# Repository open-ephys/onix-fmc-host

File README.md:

# ONIX FMC Host
This card provides a host interface for serialized headstages and miniscopes, as
well as general purpose analog and digital IO. It is a VITA-57.1
compliant module that uses high pin-count FMC connector. In combination with a
base FPGA board (e.g. [Numato Lab
Nereid](https://numato.com/product/nereid-kintex-7-pci-express-fpga-development-board),
it provides host PC communication for the following:

- Two deserailizers for any multifunction headstage conforming to the ONIX
  serialization protocol
- 12x 16-bit, +/-10V analog outputs or inputs. Direction selected via analog
  switch controllable over the FMC connector. Analog inputs are separated into
  2 simultaneously sampled 6-channel banks. 
- Analog output are always looped back using the analog inputs.
- 3x high speed LVDS input pairs
- 2x high speed LVDS outputs pairs
- 2x high speed, arbitrary logic-level, singled-ended Hi-Z or 50-ohm clock inputs
- 1x high speed single ended, 50-ohm clock output
- 4x MLVDS input or output trigger lines

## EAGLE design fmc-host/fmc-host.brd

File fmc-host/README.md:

# FMC Host PCB
Circuit design and manufacturing files for the ONIX FMC Host board.

## Bill of Materials
The bill of materials for this device can be found
[here](https://docs.google.com/spreadsheets/d/1dfK3jICU-dsLt_pm781gltwNn1_-4-RHdhAkIiad6z8/edit?usp=sharing).

## Manufacturing Requirements
In order to meet approximately correct trace impedances, the design assumes the
following stackup:

1. Top Copper 0.035 mm
1. Prepreg (2313) 0.1 mm
1. Inner Copper 0.0175 mm
1. Core (Copper) 0.565 mm
1. Inner Copper 0.0175 mm
1. Prepreg (2116) 0.127 mm
1. Inner Copper 0.0175 mm
1. Core (Copper) 0.565 mm
1. Inner Copper 0.0175 mm
1. Prepreg (2313) 0.1 mm
1. Bottom Copper 0.0175 mm

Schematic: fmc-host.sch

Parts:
C1, C2, C5, C6, C26, C27, C34, C35, C36, C37, C70, C71, C72, C73, C79, C80, C81, C91, C92, C106, C118, C139, C140: 10uF; 1206
C3, C4, C7, C8, C9, C10, C13, C14, C15, C16, C17, C18, C19, C22, C23, C30, C31, C32, C33, C41, C43, C44, C45, C46, C47, C48, C49, C52, C53, C54, C55, C56, C60, C61, C63, C65, C67, C68, C78, C83, C84, C85, C86, C87, C89, C90, C93, C99, C100, C104, C107, C110, C111, C112, C114, C115, C132, C134, C135, C137, C138: 0.1uF; 0402
C11, C12, C20, C21, C24, C25, C50, C51, C57, C58, C82, C122, C123, C124: 10nF; 0402
C28, C29: 4.7nF; 0402
C38, C39: 47nF; 0402
C40, C42, C64, C66, C74, C75, C76, C88: 1uF; 0805
C59, C62, C69, C77, C95, C96, C101, C103, C105, C108, C109, C113, C116, C117, C119, C120, C121, C125, C126, C127: 10uF; 0805
C94, C97, C98, C102, C130, C131: 47uF; 1210
C128, C129: 0.1uF, 500V; 1210
C133, C136: 33uF; 1411-VISHAY-B
D1, D2: SESD0402X1UN-0020-090; 0402P-DFN
D3, D4, D5: BAR66; SOT23
D6: KDZ4.3B; SOD123
F1, F2, F3: C014F-2; 1812
J1, J2, J3, J4, J5: SMA002; MMCX-THRU
J6: FTSH-105-01-F-D-RA-K
J7: 12226-8250-00FR; 12226-82X0-00XX
J8: FMC_SINGLE_WIDTH_MODULE
J9: ASP-134488-01; FMC_HPC_MALE
J10: BM08B-SURS-TF
L1, L2: 1008PS-472; 1008PS
L3, L4, L9, L10, L11, L12: BLM18KG601SN1D; 0603
L5, L6: SRNxx-101M; SRN6045TA
L7, L8: MPZ2012S102AT000; 0805
L13: 1277AS-H-6R8M=P2; 1210
L14, L15, L16, L17, L18, L19: BLM15PX601SN1D; 0402; PARTNO BLM15PX601SN1D
Q1, Q2: SI1012R; SC75
R1, R2, R38, R39: 3k; 0402
R3, R4, R9, R10, R57, R58: 2k; 0402
R5, R6, R7, R8, R11, R12: 150,0.25W; 0603
R13, R14, R49, R50, R51, R52, R76: 165k; 0402
R15, R16, R35, R37, R59, R64, R65, R66, R67, R68, R78, R79: 10k; 0402
R17, R18, R41, R42, R44, R45, R46, R47: 1k; 0402
R19, R21: 5.6k 1%; 0402
R20, R22: 21k 1%; 0402
R23, R24, R28, R29: 49.9; 0402
R25, R26, R27: 100; 0402
R30, R31, R32, R33, R40, R43, R71, R73, R75: 4.7k; 0402
R34, R36: DNP; 0402
R48, R63: 0; 0402
R53, R54, R55, R56: 2.2k; RN2X8-1506
R60, R61: 3.48k; 0402
R62: 649k; 0402
R69: 2.2k; 0402
R70: 15k; 0402
R72, R74: 47k; 0402
R77: 178k; 0402
R80, R81: 73.2k; 0402
S1, S2: CHS-01TA; DIP01-SMD-GULL
S3: CHS-02TB
TP1, TP2, TP4, TP5, TP6, TP7, TP11, TP12, TP13, TP14, TP15, TP16: TPB1,27; B1,27
TP3, TP8, TP9, TP10, TP17, TP18: TPB2,54; B2,54
U1: SN74LVC2G34DCKR; SC70
U2: SN65LVDS9638DGN; MSOP-8-PAD-3X3
U3: FIN1032MTCX; TSSOP-16
U4, U5: ADCMP600; SOT-23-5
U6, U7, U8: DG1412E; QFN16-4X4MM
U9, U10: DS90UB934-Q1; WQFN48-7X7-PAD
U11: DS91M040; WQFN32-5X5
U12: AD5766BCPZ-RL7; CP_40_7
U13: MCP47FEB02A0-E/ST; TSSOP-8
U14: LM4132AMF-2.5/NOPBCT-ND; SOT-23-5
U15: AD7617BSTZ; ST_80_2
U16: AD5142BCPZ10; TSSOP-16_4.4X5.0
U17: LTM4622A; BGA_5X5_625X625
U19, U20: TPS7A49; PVSON-N8+4-3X3
U21: TPS7A30; PVSON-N8+4-3X3
U22: 24AA64ST; TSSOP8
U23: LTM8049_BGA; LTM8049
U24: TPS62061DSGT; WSON8-2X2
X2: OE-LOGO_7X5; OE-LOGO-7X5

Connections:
!ADC_CS: J9.H13 (LA07_P), U15.63 (!CS)
!ADC_RESET: J9.F10 (HA08_P), R66.2
!DAC_CS: J9.J16 (HA14_N), U12.8 (!CS)
!DAC_RESET: J9.F14 (HA12_N), U12.3 (!RESET)
!LINK_PWR_ADJ_CS: J9.F38 (HB20_N), U16.16 (!CS)
!LINK_PWR_ADJ_RESET: J9.E37 (HB21_N), U16.2 (!RESET)
$N1: D5.3 (COMM), F2.2, R2.2, R6.2, R8.2, R12.2, R24.1
$N2: D3.3 (COMM), F3.2, U1.4 (OUT2), U1.6 (OUT1)
$N3: D4.3 (COMM), F1.2, R1.2, R5.2, R7.2, R11.2, R23.1
+1V8: C86.2, C87.2, C91.2, C92.2, C106.2, L3.2, L4.2, L9.1, L10.1, L13.1, R19.1, R21.1, R34.1, R36.1, TP16.TP, U9.17 (VDD18), U10.17 (VDD18), U24.4 (FB)
+3V3: C10.2, C22.1, C23.1, C28.1, C29.1, C32.1, C33.1, C74.2, C78.2, C82.2, C89.2, C93.2, C96.2, C111.2, C113.2, C114.2, C117.2, C118.2, C136.A (+), C137.2, C138.2, C139.1, C140.1, J9.E39 (VADJ), J9.F40 (VADJ), J9.G39 (VADJ), J9.H40 (VADJ), J9.J39 (VIO_B_M2C), J9.K40 (VIO_B_M2C), L11.1, L12.1, R30.2, R31.2, R32.2, R33.2, R40.2, R43.2, R57.2, R58.2, R63.1, R64.1, R65.1, R69.1, R78.2, R79.2, S1.2, S2.2, TP11.TP, U1.5 (VCC), U2.1 (VCC), U3.4 (EN), U3.16 (VCC), U4.5 (V+), U5.5 (V+), U9.4 (OSS_SEL), U9.5 (OEN), U10.4 (OSS_SEL), U10.5 (OEN), U11.11 (VDD), U11.12 (VDD), U11.29 (VDD), U11.30 (VDD), U12.4 (VLOGIC), U13.1 (VDD), U13.2 (REFA), U15.49 (VDRIVE), U16.1 (INDEP), U16.11 (VDD), U16.12 (VLOGIC), U23.A5 (VIN1), U23.A6 (VIN1), U23.A7 (VIN1), U23.B7 (RUN1), U23.K7 (RUN2), U23.L5 (VIN2), U23.L6 (VIN2), U23.L7 (VIN2), U24.5 (EN), U24.6 (MODE), U24.7 (AVIN), U24.8 (PVIN)
+5V_AN: C59.2, C62.2, C69.2, C77.2, C81.1, C83.2, C84.2, C85.2, C90.2, C107.2, C108.2, L14.1, TP1.TP, U12.28 (AVCC), U14.3 (EN), U14.4 (VIN), U15.6 (VCC), U15.15 (VCC), U15.30 (VCC), U15.71 (VCC)
+12V: C116.2, C133.A (+), C134.2, C135.2, J7.1, J7.26, J9.C35 (12P0V1), J9.C37 (12P0V2), R38.2, R39.2, TP12.TP, U17.A2 (VIN), U17.B3 (VIN), U17.D3 (VIN), U17.E2 (VIN)
+13V_AN: C7.2, C8.2, C9.2, C104.2, C105.2, L15.1, TP2.TP, U6.11 (V+), U7.11 (V+), U8.11 (V+), U12.26 (AVDD)
+15V: C130.2, L17.2, L18.2, R76.1, U23.A1 (VOUT1P), U23.A2 (VOUT1P), U23.B1 (VOUT1P), U23.B2 (VOUT1P)
-13V_AN: C17.2, C18.2, C19.2, C99.2, C103.2, L16.1, TP4.TP, U6.2 (V-), U6.PAD (V-), U7.2 (V-), U7.PAD (V-), U8.2 (V-), U8.PAD (V-), U12.6 (AVSS), U12.PAD (AVSS)
-15V: C131.1, L19.2, R77.1, U23.G1 (VOUT2N), U23.G2 (VOUT2N), U23.H1 (VOUT2N), U23.H2 (VOUT2N), U23.J2 (VOUT2N)
ADC_BUSY: J9.J12 (HA11_P), U15.67 (BUSY)
ADC_CONVST: J9.K13 (HA10_P), U15.68 (CONVST)
ADC_MISO_A: J9.K11 (HA06_N), U15.57 (DB12/SDOA)
ADC_MISO_B: J9.J10 (HA07_N), U15.56 (DB11/SDOB)
ADC_MOSI: J9.K10 (HA06_P), U15.55 (DB10/SDI)
ADC_SCLK: J9.J13 (HA11_N), U15.62 (SCLK/!RD)
ADDR0: J9.C27 (LA27_N), R78.1, S3.4
ADDR1: J9.C26 (LA27_P), R79.1, S3.3
AGND: C7.1, C8.1, C9.1, C17.1, C18.1, C19.1, C59.1, C62.1, C69.1, C77.1, C81.2, C83.1, C84.1, C85.1, C88.1, C90.1, C95.1, C99.1, C100.1, C101.1, C103.1, C104.1, C105.1, C107.1, C108.1, J7.13, J7.14, R48.1, R53.C2, R53.C4, R53.C6, R53.C7, R54.C1, R54.C3, R54.C5, R54.C6, R54.C7, R54.C8, R55.C2, R55.C3, R55.C5, R55.C7, R56.C1, R56.C2, R56.C3, R56.C4, R56.C6, R56.C8, TP3.TP, U6.3 (GND), U7.3 (GND), U8.3 (GND), U12.10 (AGND), U12.20 (NIC), U12.23 (N0), U12.24 (N1), U12.25 (NIC), U12.29 (AGND), U12.31 (NIC), U14.2 (GND), U15.5 (AGND), U15.16 (AGND), U15.29 (AGND), U15.32 (REFGND), U15.34 (REFINOUTGND), U15.69 (REGGND), U15.72 (AGND)
AIN_AOUT0: J9.F11 (HA08_N), U8.15 (IN1)
AIN_AOUT1: J9.D11 (LA05_P), U8.6 (IN4)
AIN_AOUT2: J9.E12 (HA13_P), U8.7 (IN3)
AIN_AOUT3: J9.H10 (LA04_P), U8.14 (IN2)
AIN_AOUT4: J9.E18 (HA20_P), U7.15 (IN1)
AIN_AOUT5: J9.J9 (HA07_P), U7.6 (IN4)
AIN_AOUT6: J9.G10 (LA03_N), U7.7 (IN3)
AIN_AOUT7: J9.F17 (HA15_N), U7.14 (IN2)
AIN_AOUT8: J9.H20 (LA15_N), U6.7 (IN3)
AIN_AOUT9: J9.J19 (HA18_N), U6.14 (IN2)
AIN_AOUT10: J9.G19 (LA16_N), U6.6 (IN4)
AIN_AOUT11: J9.H19 (LA15_P), U6.15 (IN1)
AIO_0: J7.7, R53.C1, U8.16 (D1)
AIO_1: J7.20, R53.C3, U8.5 (D4)
AIO_2: J7.8, R53.C5, U8.8 (D3)
AIO_3: J7.21, R53.C8, U8.13 (D2)
AIO_4: J7.9, R54.C4, U7.16 (D1)
AIO_5: J7.22, R54.C2, U7.5 (D4)
AIO_6: J7.10, R56.C5, U7.8 (D3)
AIO_7: J7.23, R56.C7, U7.13 (D2)
AIO_8: J7.11, R55.C6, U6.8 (D3)
AIO_9: J7.24, R55.C8, U6.13 (D2)
AIO_10: J7.12, R55.C4, U6.5 (D4)
AIO_11: J7.25, R55.C1, U6.16 (D1)
AOUT0: U6.1 (S1), U12.32 (VOUT0)
AOUT1: U6.4 (S4), U12.33 (VOUT1)
AOUT2: U6.9 (S3), U12.34 (VOUT2)
AOUT3: U6.12 (S2), U12.35 (VOUT3)
AOUT4: U7.1 (S1), U12.36 (VOUT4)
AOUT5: U7.4 (S4), U12.37 (VOUT5)
AOUT6: U7.12 (S2), U12.38 (VOUT6)
AOUT7: U7.9 (S3), U12.39 (VOUT7)
AOUT8: U8.9 (S3), U12.12 (VOUT8)
AOUT9: U8.12 (S2), U12.13 (VOUT9)
AOUT10: U8.4 (S4), U12.14 (VOUT10)
AOUT11: U8.1 (S1), U12.15 (VOUT11)
CLKIN0: J9.D21 (LA17_N_CC), TP7.TP, U4.1 (OUT)
CLKIN1: J9.E19 (HA20_N), TP6.TP, U5.1 (OUT)
CLKIN_TERM0: J9.K19 (HA21_P), R17.1
CLKIN_TERM1: J9.K17 (HA17_N_CC), R18.1
CLKIN_VBIAS_SCL: J9.J21 (HA22_P), R58.1, U13.7 (SCL)
CLKIN_VBIAS_SDA: J9.K20 (HA21_N), R57.1, U13.8 (SDA)
CLKOUT: J9.D20 (LA17_P_CC), U1.1 (IN3), U1.3 (IN2)
DAC_MISO: J9.K16 (HA17_P_CC), U12.9 (MISO)
DAC_MOSI: J9.H14 (LA07_N), U12.5 (MOSI)
DAC_MUX: TP15.TP, U12.27 (MUX_OUT)
DAC_SCLK: J9.J15 (HA14_P), U12.7 (SCLK)
DES_A_D0: J9.F34 (HB16_P), U10.24 (ROUT0)
DES_A_D1: J9.K35 (HB14_N), U10.23 (ROUT1)
DES_A_D2: J9.J34 (HB15_N), U10.22 (ROUT2)
DES_A_D3: J9.K34 (HB14_P), U10.21 (ROUT3)
DES_A_D4: J9.E33 (HB19_P), U10.19 (ROUT4)
DES_A_D5: J9.J33 (HB15_P), U10.18 (ROUT5)
DES_A_D6: J9.F32 (HB12_N), U10.16 (ROUT6)
DES_A_D7: J9.E31 (HB13_N), U10.15 (ROUT7)
DES_A_D8: J9.K32 (HB10_N), U10.14 (ROUT8)
DES_A_D9: J9.F31 (HB12_P), U10.13 (ROUT9)
DES_A_D10: J9.J31 (HB11_N), U10.12 (ROUT10)
DES_A_D11: J9.K31 (HB10_P), U10.11 (ROUT11)
DES_A_GPIO0: J9.J37 (HB18_N), U10.28 (GPIO0)
DES_A_GPIO1: J9.K37 (HB17_P_CC), U10.27 (GPIO1)
DES_A_GPIO2: J9.J36 (HB18_P), U10.26 (GPIO2)
DES_A_GPIO3: J9.E34 (HB19_N), R43.1, U10.25 (GPIO3/INTB)
DES_A_HSYNC: J9.E30 (HB13_P), U10.10 (HSYNC)
DES_A_LOCK: J9.E27 (HB09_P), R50.2, U10.48 (LOCK)
DES_A_PASS: J9.J28 (HB07_N), R52.2, U10.47 (PASS)
DES_A_PCLK: J9.K28 (HB06_P_CC), U10.8 (PCLK)
DES_A_PDB: J9.F35 (HB16_N), U10.30 (PDB)
DES_A_SCL: J9.F29 (HB08_N), R31.1, U10.2 (SCL)
DES_A_SDA\: J9.E28 (HB09_N), R33.1, U10.1 (SDA)
DES_A_VSYNC: J9.J30 (HB11_P), U10.9 (VSYNC)
DES_B_D0: J9.H29 (LA24_N), U9.24 (ROUT0)
DES_B_D1: J9.H28 (LA24_P), U9.23 (ROUT1)
DES_B_D2: J9.G28 (LA25_N), U9.22 (ROUT2)
DES_B_D3: J9.G27 (LA25_P), U9.21 (ROUT3)
DES_B_D4: J9.D27 (LA26_N), U9.19 (ROUT4)
DES_B_D5: J9.D26 (LA26_P), U9.18 (ROUT5)
DES_B_D6: J9.H26 (LA21_N), U9.16 (ROUT6)
DES_B_D7: J9.G25 (LA22_N), U9.15 (ROUT7)
DES_B_D8: J9.H25 (LA21_P), U9.14 (ROUT8)
DES_B_D9: J9.D24 (LA23_N), U9.13 (ROUT9)
DES_B_D10: J9.G24 (LA22_P), U9.12 (ROUT10)
DES_B_D11: J9.D23 (LA23_P), U9.11 (ROUT11)
DES_B_GPIO0: J9.H32 (LA28_N), U9.28 (GPIO0)
DES_B_GPIO1: J9.G31 (LA29_N), U9.27 (GPIO1)
DES_B_GPIO2: J9.H31 (LA28_P), U9.26 (GPIO2)
DES_B_GPIO3: J9.G30 (LA29_P), R40.1, U9.25 (GPIO3/INTB)
DES_B_HSYNC\: J9.H23 (LA19_N), U9.10 (HSYNC)
DES_B_LOCK: J9.J22 (HA22_N), R49.2, U9.48 (LOCK)
DES_B_PASS: J9.K22 (HA23_P), R51.2, U9.47 (PASS)
DES_B_PCLK: J9.C22 (LA18_P_CC), U9.8 (PCLK)
DES_B_PDB: J9.G33 (LA31_P), U9.30 (PDB)
DES_B_SCL: J9.G22 (LA20_N), R30.1, U9.2 (SCL)
DES_B_SDA: J9.H22 (LA19_P), R32.1, U9.1 (SDA)
DES_B_VSYNC: J9.K23 (HA23_N), U9.9 (VSYNC)
DI_VBIAS0: R15.1, U13.3 (VOUT0)
DI_VBIAS1: R16.1, U13.4 (VOUT1)
DOUTP_F_A: C45.2, D2.C, J2.SIG (1), L2.2, R4.2
DOUTP_F_B: C44.2, D1.C, J1.SIG (1), L1.2, R3.2
FMC_PG: J9.D1 (PG_C2M), J9.F1 (PG_M2C)
GND: C1.1, C2.1, C3.1, C4.1, C5.1, C6.1, C10.1, C11.1, C12.1, C13.2, C14.2, C15.2, C16.2, C20.1, C21.1, C22.2, C23.2, C24.1, C25.1, C26.1, C27.1, C28.2, C29.2, C30.2, C31.2, C32.2, C33.2, C34.1, C35.1, C36.1, C37.1, C40.1, C41.1, C42.1, C43.1, C46.1, C47.1, C48.1, C49.1, C50.1, C51.1, C52.1, C53.1, C54.1, C55.1, C56.1, C57.1, C58.1, C60.1, C61.1, C63.1, C64.1, C65.1, C66.1, C67.1, C68.1, C70.1, C71.1, C72.1, C73.1, C74.1, C75.1, C76.1, C78.1, C79.1, C80.1, C82.1, C86.1, C87.1, C89.1, C91.1, C92.1, C93.1, C94.1, C96.1, C97.1, C98.1, C102.1, C106.1, C109.1, C110.1, C111.1, C112.1, C113.1, C114.1, C115.2, C116.1, C117.1, C118.1, C119.1, C120.1, C121.1, C122.2, C123.2, C124.2, C125.1, C126.1, C127.1, C128.1, C129.1, C130.1, C131.2, C132.1, C133.C (-), C134.1, C135.1, C136.C (-), C137.1, C138.1, C139.2, C140.2, D1.A, D2.A, D3.1 (A), D4.1 (A), D5.1 (A), D6.A, J1.GND@1 (2), J1.GND@2 (2), J1.GND@3 (2), J1.GND@4 (2), J2.GND@1 (2), J2.GND@2 (2), J2.GND@3 (2), J2.GND@4 (2), J3.GND@1 (2), J3.GND@2 (2), J3.GND@3 (2), J3.GND@4 (2), J4.GND@1 (2), J4.GND@2 (2), J4.GND@3 (2), J4.GND@4 (2), J5.GND@1 (2), J5.GND@2 (2), J5.GND@3 (2), J5.GND@4 (2), J7.PAD1, J7.PAD2, J9.A1 (GND), J9.A4 (GND), J9.A5 (GND), J9.A8 (GND), J9.A9 (GND), J9.A12 (GND), J9.A13 (GND), J9.A16 (GND), J9.A17 (GND), J9.A20 (GND), J9.A21 (GND), J9.A24 (GND), J9.A25 (GND), J9.A28 (GND), J9.A29 (GND), J9.A32 (GND), J9.A33 (GND), J9.A36 (GND), J9.A37 (GND), J9.A40 (GND), J9.B2 (GND), J9.B3 (GND), J9.B6 (GND), J9.B7 (GND), J9.B10 (GND), J9.B11 (GND), J9.B14 (GND), J9.B15 (GND), J9.B18 (GND), J9.B19 (GND), J9.B22 (GND), J9.B23 (GND), J9.B26 (GND), J9.B27 (GND), J9.B30 (GND), J9.B31 (GND), J9.B34 (GND), J9.B35 (GND), J9.B38 (GND), J9.B39 (GND), J9.C1 (GND), J9.C4 (GND), J9.C5 (GND), J9.C8 (GND), J9.C9 (GND), J9.C12 (GND), J9.C13 (GND), J9.C16 (GND), J9.C17 (GND), J9.C20 (GND), J9.C21 (GND), J9.C24 (GND), J9.C25 (GND), J9.C28 (GND), J9.C29 (GND), J9.C32 (GND), J9.C33 (GND), J9.C34 (GA0), J9.C36 (GND), J9.C38 (GND), J9.C40 (GND), J9.D2 (GND), J9.D3 (GND), J9.D6 (GND), J9.D7 (GND), J9.D10 (GND), J9.D13 (GND), J9.D16 (GND), J9.D19 (GND), J9.D22 (GND), J9.D25 (GND), J9.D28 (GND), J9.D35 (GA1), J9.D37 (GND), J9.D39 (GND), J9.E1 (GND), J9.E4 (GND), J9.E5 (GND), J9.E8 (GND), J9.E11 (GND), J9.E14 (GND), J9.E17 (GND), J9.E20 (GND), J9.E23 (GND), J9.E26 (GND), J9.E29 (GND), J9.E32 (GND), J9.E35 (GND), J9.E38 (GND), J9.E40 (GND), J9.F2 (GND), J9.F3 (GND), J9.F6 (GND), J9.F9 (GND), J9.F12 (GND), J9.F15 (GND), J9.F18 (GND), J9.F21 (GND), J9.F24 (GND), J9.F27 (GND), J9.F30 (GND), J9.F33 (GND), J9.F36 (GND), J9.F39 (GND), J9.G1 (GND), J9.G4 (GND), J9.G5 (GND), J9.G8 (GND), J9.G11 (GND), J9.G14 (GND), J9.G17 (GND), J9.G20 (GND), J9.G23 (GND), J9.G26 (GND), J9.G29 (GND), J9.G32 (GND), J9.G35 (GND), J9.G38 (GND), J9.G40 (GND), J9.H2 (PRSNT_M2C_L), J9.H3 (GND), J9.H6 (GND), J9.H9 (GND), J9.H12 (GND), J9.H15 (GND), J9.H18 (GND), J9.H21 (GND), J9.H24 (GND), J9.H27 (GND), J9.H30 (GND), J9.H33 (GND), J9.H36 (GND), J9.H39 (GND), J9.J1 (GND), J9.J4 (GND), J9.J5 (GND), J9.J8 (GND), J9.J11 (GND), J9.J14 (GND), J9.J17 (GND), J9.J20 (GND), J9.J23 (GND), J9.J26 (GND), J9.J29 (GND), J9.J32 (GND), J9.J35 (GND), J9.J38 (GND), J9.J40 (GND), J9.K2 (GND), J9.K3 (GND), J9.K6 (GND), J9.K9 (GND), J9.K12 (GND), J9.K15 (GND), J9.K18 (GND), J9.K21 (GND), J9.K24 (GND), J9.K27 (GND), J9.K30 (GND), J9.K33 (GND), J9.K36 (GND), J9.K39 (GND), J10.2, J10.6, Q1.2 (S), Q2.2 (S), R1.1, R2.1, R13.1, R14.1, R20.2, R22.2, R28.2, R29.2, R35.2, R37.2, R48.2, R49.1, R50.1, R51.1, R52.1, R62.2, R67.2, R68.2, R71.1, R73.1, R75.1, R80.2, R81.2, S3.1, S3.2, TP8.TP, TP9.TP, TP10.TP, TP17.TP, TP18.TP, U1.2 (GND), U2.4 (GND), U2.PAD (GND), U3.8 (GND), U3.12 (!EN), U4.2 (V-), U5.2 (V-), U9.43 (RES1), U9.44 (RES2), U9.46 (SEL), U9.PAD (GND), U10.43 (RES1), U10.44 (RES2), U10.46 (SEL), U10.PAD (GND), U11.31 (GND), U11.PAD (GND), U12.2 (DGND), U13.5 (AVSS), U13.6 (LAT/HVC), U15.37 (SEQEN), U15.38 (HW_RNGSEL1), U15.39 (HW_RNGSEL0), U15.41 (DB0), U15.42 (DB1), U15.43 (DB2), U15.44 (DB3), U15.46 (DB5/CRCEN), U15.47 (DB6), U15.48 (DB7), U15.50 (DGND), U15.51 (REGGNDD), U15.53 (DB8), U15.54 (DB9), U15.58 (DB13/OS0), U15.59 (DB14/OS1), U15.60 (DB15/OS2), U15.61 (WR!/BURST), U15.64 (CHSEL0), U15.65 (CHSEL1), U15.66 (CHSEL2), U16.3 (GND), U16.5 (W1), U16.7 (VSS), U16.9 (W2), U17.B5 (GND), U17.C1 (GND), U17.C2 (GND), U17.C5 (SYNC/MODE), U17.D5 (GND), U19.3 (NC), U19.4 (GND), U19.PAD1 (PAD), U19.PAD2 (PAD), U19.PAD3 (PAD), U19.PAD4 (PAD), U19.PAD5 (PAD), U20.3 (NC), U20.4 (GND), U20.PAD1 (PAD), U20.PAD2 (PAD), U20.PAD3 (PAD), U20.PAD4 (PAD), U20.PAD5 (PAD), U21.3 (NC), U21.4 (GND), U21.PAD1 (PAD), U21.PAD2 (PAD), U21.PAD3 (PAD), U21.PAD4 (PAD), U21.PAD5 (PAD), U22.1 (A0), U22.2 (A1), U22.3 (A2), U22.4 (GND), U22.7 (WP), U23.A3 (GND), U23.A4 (GND), U23.B3 (GND), U23.B4 (GND), U23.B5 (GND), U23.B6 (GND), U23.C2 (VOUT1N), U23.C3 (GND), U23.C4 (GND), U23.C5 (GND), U23.C6 (GND), U23.D1 (VOUT1N), U23.D2 (VOUT1N), U23.D3 (GND), U23.D4 (GND), U23.D5 (GND), U23.D7 (SYNC1), U23.E1 (VOUT1N), U23.E2 (VOUT1N), U23.E3 (GND), U23.E4 (GND), U23.E5 (GND), U23.F1 (GND), U23.F2 (GND), U23.F5 (GND), U23.F6 (GND), U23.F7 (GND), U23.G3 (GND), U23.G4 (GND), U23.G5 (GND), U23.H3 (GND), U23.H4 (GND), U23.H5 (GND), U23.J3 (GND), U23.J4 (GND), U23.J5 (GND), U23.J6 (GND), U23.K1 (VOUT2P), U23.K2 (VOUT2P), U23.K3 (GND), U23.K4 (GND), U23.K5 (GND), U23.K6 (GND), U23.L1 (VOUT2P), U23.L2 (VOUT2P), U23.L3 (GND), U23.L4 (GND), U24.1 (PGND), U24.3 (AGND), U24.PAD (AGND)
LINK_A_PWR_EN: J9.H37 (LA32_P), R68.1, U17.B2 (RUN2)
LINK_B_PWR_EN: J9.K38 (HB17_N_CC), R67.1, U17.D2 (RUN1)
LINK_PWR_ADJ_MISO: J9.F37 (HB20_P), R69.2, U16.15 (MISO)
LINK_PWR_ADJ_MOSI: J9.E36 (HB21_P), U16.14 (MOSI)
LINK_PWR_ADJ_SCLK: J9.H38 (LA32_N), U16.13 (SCLK)
LVDS_DIN0: J9.J2 (CLK3_M2C_P), U3.3 (AOUT)
LVDS_DIN0_N: J7.4, R25.1, U3.1 (A-)
LVDS_DIN0_P: J7.17, R25.2, U3.2 (A+)
LVDS_DIN1: J9.H5 (CLK0_M2C_N), U3.5 (BOUT)
LVDS_DIN1_N: J7.16, R26.1, U3.7 (B-)
LVDS_DIN1_P: J7.3, R26.2, U3.6 (B+)
LVDS_DIN2: J9.H4 (CLK0_M2C_P), U3.11 (COUT)
LVDS_DIN2_N: J7.2, R27.1, U3.9 (C-)
LVDS_DIN2_P: J7.15, R27.2, U3.10 (C+)
LVDS_DOUT0: J9.J3 (CLK3_M2C_N), U2.2 (AIN)
LVDS_DOUT0_N: J7.19, U2.7 (AOUT-)
LVDS_DOUT0_P: J7.6, U2.8 (AOUT+)
LVDS_DOUT1: J9.K4 (CLK2_M2C_P), U2.3 (BIN)
LVDS_DOUT1_N: J7.18, U2.5 (BOUT-)
LVDS_DOUT1_P: J7.5, U2.6 (BOUT+)
MLVDS_CLK_0_N: J6.10, U11.24 (B0)
MLVDS_CLK_0_P: J6.09 (9), U11.23 (A0)
MLVDS_CLK_1_N: J6.08 (8), U11.22 (B1)
MLVDS_CLK_1_P: J6.07 (7), U11.21 (A1)
MLVDS_CLK_2_N: J6.04 (4), U11.20 (B2)
MLVDS_CLK_2_P: J6.03 (3), U11.19 (A2)
MLVDS_CLK_3_N: J6.02 (2), U11.18 (B3)
MLVDS_CLK_3_P: J6.01 (1), U11.17 (A3)
MLVDS_DE_!RE0: J9.F7 (HA04_P), U11.25 (DE0), U11.26 (!RE0)
MLVDS_DE_!RE1: J9.E7 (HA05_N), U11.27 (DE1), U11.28 (!RE1)
MLVDS_DE_!RE2: J9.H7 (LA02_P), U11.13 (!RE2), U11.14 (DE2)
MLVDS_DE_!RE3: J9.H8 (LA02_N), U11.15 (!RE3), U11.16 (DE3)
MLVDS_DI0: J9.F5 (HA00_N_CC), U11.2 (DI0)
MLVDS_DI1: J9.E2 (HA01_P_CC), U11.4 (DI1)
MLVDS_DI2: J9.E3 (HA01_N_CC), U11.6 (DI2)
MLVDS_DI3: J9.G3 (CLK1_M2C_N), U11.8 (DI3)
MLVDS_EN: J9.F8 (HA04_N), U11.10 (MDE)
MLVDS_RO0: J9.F4 (HA00_P_CC), U11.1 (RO0)
MLVDS_RO1: J9.G6 (LA00_P_CC), U11.3 (RO1)
MLVDS_RO2: J9.G7 (LA00_N_CC), U11.5 (RO2)
MLVDS_RO3: J9.G2 (CLK1_M2C_P), U11.7 (RO3)
unnamed: L13.2, U24.2 (SW)
unnamed: Q1.3 (D), R5.1, R7.1, R11.1
unnamed: R23.2, U4.3 (+IN)
unnamed: L1.1, L5.2, R3.1, R9.2
unnamed: R61.1, U17.A4 (FB2)
unnamed: F2.1, J4.SIG (1)
unnamed: Q2.3 (D), R6.1, R8.1, R12.1
unnamed: C110.2, U17.A3 (TRACK/SS2)
unnamed: R81.1, U23.G7 (RT2)
unnamed: R60.1, U17.E4 (FB1)
unnamed: F1.1, J3.SIG (1)
unnamed: C112.2, U17.E3 (TRACK/SS1)
unnamed: F3.1, J5.SIG (1)
unnamed: C125.2, L17.1, U19.5 (EN), U19.8 (IN)
unnamed: R80.1, U23.E7 (RT1)
unnamed: C13.1, R15.2, U4.4 (-IN)
unnamed: R24.2, U5.3 (+IN)
unnamed: C14.1, R16.2, U5.4 (-IN)
unnamed: L2.1, L6.2, R4.1, R10.2
unnamed: C6.2, C16.1, L6.1, L8.2, R10.1
unnamed: R55.1, U15.79 (V3B)
unnamed: C5.2, C15.1, L5.1, L7.2, R9.1
unnamed: R77.2, U23.J1 (FBX2)
unnamed: C45.1, U10.41 (RIN0+)
unnamed: C39.1, U10.42 (RIN0-)
unnamed: R76.2, U23.C1 (FBX1)
unnamed: C36.2, C42.2, C47.2, U10.3 (VDD11_D)
unnamed: C37.2, C43.2, U10.20 (VDD11_DVP)
unnamed: C39.2, R29.1
unnamed: C122.1, U19.6 (NR/SS)
unnamed: Q2.1 (G), R14.2, R18.2
unnamed: U23.E6 (CLKOUT1), U23.H7 (SYNC2)
unnamed: Q1.1 (G), R13.2, R17.2
unnamed: C44.1, U9.41 (RIN0+)
unnamed: R55.2, U15.80 (V3BGND)
unnamed: R70.1, R71.2, U19.2 (FB)
unnamed: C126.2, L18.1, U20.5 (EN), U20.8 (IN)
unnamed: C123.1, U20.6 (NR/SS)
unnamed: C68.2, C76.2, C80.2, U10.34 (VDD11_FPD)
unnamed: C115.1, R66.1, U15.36 (!RESET)
unnamed: C55.2, C60.2, C64.2, C71.2, L11.2, U9.7 (VDDIO), U9.29 (VDDIO)
unnamed: C34.2, C40.2, C46.2, U9.3 (VDD11_D)
unnamed: C35.2, C41.2, U9.20 (VDD11_DVP)
unnamed: C67.2, C75.2, C79.2, U9.34 (VDD11_FPD)
unnamed: C129.2, J9.CHASSIS_B (STANDOFF_B)
unnamed: C128.2, J9.CHASSIS_A (STANDOFF_A)
unnamed: J10.5, R42.2
unnamed: C38.1, U9.42 (RIN0-)
unnamed: R72.1, R73.2, U20.2 (FB)
unnamed: J10.7, R47.1
unnamed: C127.2, L19.1, U21.5 (EN), U21.8 (IN)
unnamed: C124.1, U21.6 (NR/SS)
unnamed: R74.1, R75.2, U21.2 (FB)
unnamed: R65.2, U15.45 (DB4/!SER1WR)
unnamed: R53.1, U15.28 (V0A)
unnamed: R64.2, U15.40 (SER/!PAR)
unnamed: C95.2, U15.31 (REFCAP)
unnamed: R53.2, U15.27 (V0AGND)
unnamed: J10.8, R41.1
unnamed: C109.2, U15.52 (REGCAPD)
unnamed: R55.8, U15.73 (V0B)
unnamed: C101.2, U15.70 (REGCAP)
unnamed: R63.2, U15.35 (REFSEL)
unnamed: R56.7, U15.2 (V4B)
unnamed: R56.1, U15.10 (V7BGND)
unnamed: R55.7, U15.74 (V0BGND)
unnamed: R55.6, U15.75 (V1B)
unnamed: R55.5, U15.76 (V1BGND)
unnamed: R55.4, U15.77 (V2B)
unnamed: R55.3, U15.78 (V2BGND)
unnamed: R53.3, U15.26 (V1A)
unnamed: R53.4, U15.25 (V1AGND)
unnamed: R53.5, U15.24 (V2A)
unnamed: R53.6, U15.23 (V2AGND)
unnamed: R53.8, U15.22 (V3A)
unnamed: R53.7, U15.21 (V3AGND)
unnamed: R54.2, U15.19 (V4A)
unnamed: R54.1, U15.20 (V4AGND)
unnamed: R54.4, U15.17 (V5A)
unnamed: R54.3, U15.18 (V5AGND)
unnamed: R54.5, U15.14 (V6A)
unnamed: R54.6, U15.13 (V6AGND)
unnamed: R54.7, U15.12 (V7A)
unnamed: R54.8, U15.11 (V7AGND)
unnamed: C38.2, R28.1
unnamed: R56.8, U15.1 (V4BGND)
unnamed: R56.5, U15.4 (V5B)
unnamed: R56.6, U15.3 (V5BGND)
unnamed: R56.4, U15.7 (V6B)
unnamed: R56.3, U15.8 (V6BGND)
unnamed: R56.2, U15.9 (V7B)
unnamed: R34.2, R35.1, U9.35 (IDX)
unnamed: J10.4, R45.1
unnamed: J10.3, R46.1
unnamed: J10.1, R44.1
unnamed: R60.2, U16.4 (A1)
unnamed: R61.2, U16.8 (A2)
unnamed: R62.1, U17.C4 (FREQ)
unnamed: C56.2, C61.2, C66.2, C73.2, L12.2, U10.7 (VDDIO), U10.29 (VDDIO)
unnamed: S2.1, U10.6 (BISTEN)
unnamed: R21.2, R22.1, U10.37 (MODE)
unnamed: R36.2, R37.1, U10.35 (IDX)
unnamed: C119.2, L14.2, R70.2, U19.1 (OUT)
unnamed: C120.2, L15.2, R72.2, U20.1 (OUT)
unnamed: C121.2, L16.2, R74.2, U21.1 (OUT)
unnamed: C100.2, R59.1, U15.33 (REFINOUT)
unnamed: S1.1, U9.6 (BISTEN)
unnamed: R19.2, R20.1, U9.37 (MODE)
PORT_A_BLUE: J9.G18 (LA16_P), R41.2
PORT_A_GREEN: J9.J18 (HA18_P), R47.2
PORT_A_RED: J9.H17 (LA11_N), R42.1
PORT_B_BLUE: J9.H16 (LA11_P), R45.2
PORT_B_GREEN: J9.G15 (LA12_P), R46.2
PORT_B_RED: J9.G13 (LA08_N), R44.2
SCL: J9.C30 (SCL), U22.6 (SCL)
SDA: J9.C31 (SDA), U22.5 (SDA)
TDI-TDO: J9.D30 (TDI), J9.D31 (TDO)
VAUX: C132.2, J9.D32 (3P3VAUX), U22.8 (VCC)
VDD_FPDX_A: C2.2, C4.2, C12.2, C21.2, C25.2, L4.1, U10.31 (VDD18_FPD1), U10.40 (VDD18_FPD0)
VDD_FPDX_B: C1.2, C3.2, C11.2, C20.2, C24.2, L3.1, U9.31 (VDD18_FPD1), U9.40 (VDD18_FPD0)
VDD_PX_A: C49.2, C51.2, C54.2, C58.2, C65.2, C72.2, L10.2, U10.36 (VDD18_P1), U10.45 (VDD18_P0)
VDD_PX_B: C48.2, C50.2, C53.2, C57.2, C63.2, C70.2, L9.2, U9.36 (VDD18_P1), U9.45 (VDD18_P0)
VLINK_A: C27.2, C31.1, C94.2, C97.2, L8.1, TP13.TP, U17.A1 (VOUT2), U17.B1 (VOUT2)
VLINK_B: C26.2, C30.1, C98.2, C102.2, L7.1, TP14.TP, U17.D1 (VOUT1), U17.E1 (VOUT1)
VREF: C88.2, R59.2, U12.22 (VREF), U14.5 (VOUT)
V_PROTECT: C52.2, D3.2 (C), D4.2 (C), D5.2 (C), D6.C, R38.1, R39.1, TP5.TP

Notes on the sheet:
FMC MEZZANINE
NB: Input protection voltage ~4.6V
L2 is the smallest package size I could find that barely meets current saturation requriements. An 8x8mm device that is probably safer is the Bourns SRN8040TA series.
Power: ~1.3A DC at 12V; 15.6W. With 90% efficiency regulation to 5.5V at serializer, this translates to 2.55A available, which is enough for 1A/LED + 500 mA serializer and FPGA.
DNP
NB: Use both MISO lines
NB: R-arrays provide input protection. Limit current thru internal clamp diodes to 10 mA at 20V.
NB: Worst case 100 mA draw from both ADC and DAC. With 10V stepdown, this is 1W dissipation.
ANALOG IO
CLOCK IO
NB: 3.48k = 11V output.
NB: VADJ must be set to 1.8V on host board!
NB: GA0 and GA1 define the LSBs of the EEPROM I2C address. We use 0x1010000
NB: FMC FRU module. Required by FMC standard.
Quad 1
Quad 2
Quad 3
NB: For best performance, quads should only be input or output, not mixtures.
TP1
TP2
TP3
TP4
TP5
NB: VLINK adjust. - Max step down ratio: 1 - (45e-9 *1.48e6) = 0.933 - So max voltage = 11.19 - Linear mode selected - R_AW = 0 : VLINK = 11.0V - R_AW = 5k : VLINK = 5.0V - General: VLINK = 36.24k/(3.48k + R_AW) + 0.6
NB: Default VBIAS = 1.65V
LINK A
LINK POWER
ANALOG POWER
LINK B
CLK IN 0
CLK IN 1
CLK OUT
FMC IO
HPC FMC
SYNC. TRIG.
SYNC
NB: Board address
NB: P,N order matches SDR datasheet spec.
NB: DC signals so no worries about DGND
NB: All IO to to CC Pin or better

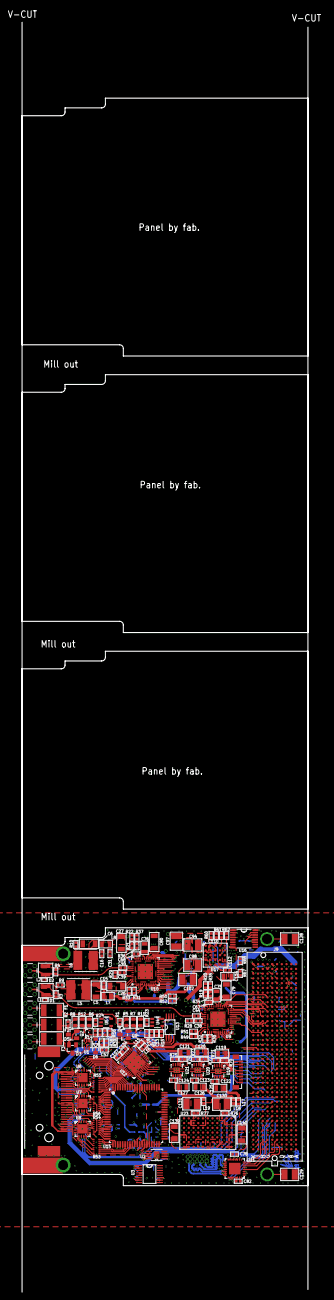
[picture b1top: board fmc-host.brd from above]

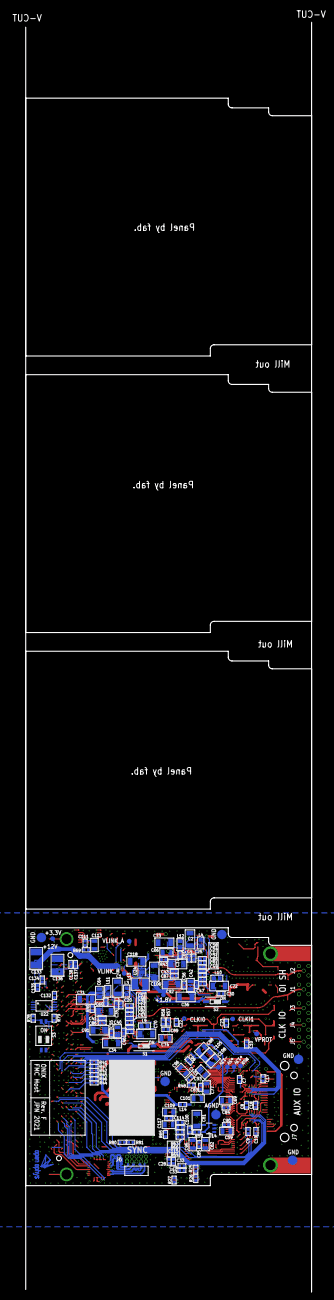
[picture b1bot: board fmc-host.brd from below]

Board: 6 copper layers, 76.5 x 339.8 mm, 306 parts (152 on the bottom side), 294 nets.

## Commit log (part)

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2019-01-20 FMC host module
    - This will deprecate pcie-host
    - Should conform, largely, to VITA-57 standardFeatures
    - 1 deserializer
    - 2 arbitrary logic-level rugged GPIs
    - 1 arbitrary logic-level rugged GPO
    - 8 16-bit analog outputs
2019-01-20 Updates to fmc-host board
    - Added header for debug (need to connect still)
    - All test points to bottom
    - Silk screen improvements
2019-01-21 Completed fmc-host board
    - Added debug port that can be plugged into logic analyzer
    - Added pdf of schematic
    - Small silkscreen and routing changes
2019-01-23 fmc-host board v1.0
    - Ready for fabrication
    - BOM simplification
    - Part renumber
    - Silkscreen update
2019-01-25 Update READMEs to capture current state of project
    - fmc-host board
    - analog-io-board
    - pcie-host board removed from top level README
    - License files added where needed
2019-03-04 fmc-host updates after assembly
    - Mostly small layout changes to fix incorrect land patterns, shorts,
    etc.
    - Now we are using external reference for ADC and DAC instead of using
    ADC's
2019-03-05 Final updates to fmc-host rev 1.1
    - Changes reflect issues found during assembly
2019-03-05 Changed microstrip on fmc-host to match JLCPCB impednace specs
    - Using JLC7628
    - 50 Ohm trace is 0.3 mm thick (outer layer and first ground plane)
2019-05-07 Initial commit of 3d printed case for pcie fmc host Designed to slot into the FMC card and then screw into the numato board Many features and dimensions are still missing
2019-05-08 Tweaked pcie system case for initial test print
2019-05-23 Updated fmc pcie case - Fixed screw hole sizes (hopefully) - Less 90s design - Changed to 12mm FMC stack height
2019-07-28 Initial schematic for fmc-host rev. 1.1
    - High pincount FMC
    - Lots of feature additions and deprecations after learning from rev.
    1.0
    - 2x deserializers instead of 1
    - Remove 20 Ohm series impedance matching resistors from deserializer
    parallel connection because they are not needed
2019-07-30 Initial component placement for fmc-host rev. 1.1
    - 6 layer board with 2 high speed layers
    - Initial routing
    - Added a TODO file to the enclosure folder
2019-08-02 fmc-host rev 1.1 routing progress
    - Labelled all FMC pin connections by IO type and clock capability
    - Almost completely routed analog section (ADC, DAC, and muxing)
    - Starting to bring back digital IO to dummy vias on FMC for arrangement
2019-08-09 Initial FMC pinout largely decided
    - XDC file contains the pinout
    - Need to test sythesis before fully committing and finishing board
    routing
2019-08-12 fmc-host rev. 1.1
    - Completed revision 1.1 of the FMC host module
    - Needs final synthesis testing before fab
2019-08-15 Small fixes to silk layer on fmc-host rev 1.1
    - Should be ready for fabrication
    - Added some gerber art to gerber folder
2019-08-26 Replace SMD MMCX with thru hole on fmc-host
    - Less likely to rip off
    - Also, got rid of redundant ground vias around these connectors
2019-09-23 FMC host board rev. 1.3
    - Some minor changes after building revision 1.2 and implementing FPGA
    design
    - DES_A_PCLK moved to positive pin
    - Swapped DES_B_D[1] and DES_B_D[2]
    - Minor fixes to packages
    - BOM simplification
2019-09-29 Added CNCd PCIe bracket for FMC host
2019-09-30 Added text to pcie bracket
2019-09-30 Added STL of fmc-host PCIe bracket
2019-11-17 Updates to fmc-host board when testing revision 1.3
    - This is starting revision 1.4
    - Replaced SPDT analog switches for analog IO with SPST swiches inline
    with the analog outpus. Inputs are always connected. This allows
    loopback of analog output instead of wasting the analog input
    capabilites when a line is selected to be an output
2019-12-07 headstage-neuropix rev 1.2
    - Dual neuropixels probe support
    - 2X HTC Vive receivers
    - Many changes made for reliability of manufacturing
2020-01-06 fmc-host board rev. 1.4
    - Several small but significant changes to rev. 1.3
    - DES LOCK and PASS lines have pull down resistors now to deal with the
    fact that they are tri-stated when the DES is in PDN mode
    - PDN pin directly driven by FPGA instead of unnecessary FET
2020-02-07 fmc-host rev. 1.3
    - This revision of the fmc-host board addresses several issues
    encountered during testing of revision 1.2
    - The deserializers have been upgrated to DS90UB934-Q1s. This increases
    the forward channel bandwidth to 14 x 100 MHz and reduces back channel
    latency.
    - The SPDT analog switches on rev. 1.2 have been replaced with SDST
2020-02-07 Minor BOM simplifications to fmc-host rev. 1.3
2020-02-07 Updated PCIe mounting bracket
    - Increased FMC standoff form 10 to 12mm
    - Added holes for LEDs
    - Fixed markings
2020-02-09 Address Filipe's suggestions prior to fabrication
    - Use grid of cream bloks under QFN center pads instead of one large
    one. Place vias between these blocks where possible
    - Improve silk layer readability
    - Move copper away from dimension in several areas
    - Add SMD mount files
2020-02-09 Remove erroneos LED values from silk layer of fmc-host
2020-02-09 Move silk out from under components where possible in fmc-host
    - Bad practice, esp for passives, due to increase tombstoning risk
2020-02-12 Fixed LED cutouts for FMC and added little divider
2020-04-02 Added RGB LEDs and driver to breakout-board
    - The old circuit, with single green LEDs driven by the TCA9555 is still
    there and functional if this circuit is not populated
    - If it is, the LED outputs on the TCA should be set to hiZ
2020-06-08 Minor updates to fmc-host
    - Fix analog IO select mapping
    - Added html bom
2020-07-13 Added frozen fmc-host revision 1.4
    - This is the revision that was produced by OEPS for distribution with
    the beta test
2020-07-13 Started fmc-host revision 1.5
    - Added missing 2.2k pullup resistor to the MISO lines of the dual
    potentiometer, which is an open drain pin
2020-07-13 Got rid of accidentally added temporary files
2020-07-14 Moved the pullup resistor on fmc-host's pot's SDO line away from hole
    - It was too close to the FMC mounting hole and would have been smashed
    by the standoff
2020-08-28 Move entire repository to CC BY-NC-SA 4.0
2020-10-19 Added frozen fmc-host revision 1.3
    - This is a prototype version that uses the ds90ub914a deserialzer and a
    different muxing scheme from more modern variants on the analog IO
    - It is pretty widely used in the Harnett and Wilson labs
2020-10-20 Fix several issues while testing fmc-host rev 1.4
    - VADJ on the FMC connector determines the IO voltage of all the "A"
    pins on the FMC connector, and therefore chips driving or receiving from
    these lines must use VADJ for their IO voltage.
    - The IO voltage of all "B" pins on the FMC connector is determined by
    VIO_B_M2C, so I'm feeding VADJ right back into that pin.
    - The 1.8V core voltage for the deserializers is now derived from VADJ
2021-06-25 Moved fmc-host into independent repo
    - Did some reorganization as well to make it a bit more like the
    onix-headstage-neuropix1 repo
2021-06-26 Update README.md
    - Delete redundant BOM and stackup info that can now be found in fmc-host/README.md
2021-06-26 Replaced revisions folders with tags
    - Tags are rev-1.3 and rev-1.4
2021-06-28 ONIX FMC Host revision 1.5
    - Lots of minor fixes after extensive testing of 1.4
    - VITA-57 compliance
    - Remove debug points
    - Standalone 1.8V regulator for deserializers
    - Lots of other small fixes
2021-07-10 Revision 1.6
    - The major change here is that I've swapped the vertical MVLVDS sync
    header for a through-hole right-angle version that is much more
    amenable to daisy chain connections when the card is in a PCIe slot.
    - Deleted some obsolete, hard to maintain files
    - Deleted some obsolete datasheets
2021-07-17 Move datasheets into fmc-host directory
2021-07-18 Add .gitignore
2021-09-01 Add license
    - CC BY-NC-SA 4.0
2021-10-25 Redesign of the PCIe bracket
    - Fixed incorrect distances
    - Added inserts for 5mm RGB LEDs for better panel lighting to work wirht
    revision 1.6 (Rev. F)
    - Two versions 2.0 mm and 1.27 mm thick. 2.0 is probably the only
    reasonable one for 3D printing.
    - Shapeways DGPA12GB (Dark Grey PA12 with glass beads) has excellent
2021-10-27 Update PCIe bracket after testing
    - Move the FMC supports to the inside and make them solid
    - Make the the portions of the bracket that must interface with the card
    slot thinner to give them a better chance of working (the part should
    really be 0.8mm thick)
2022-03-09 Revision F ready for fabrication feedback
    - Replaced QFN AD5142 with TSSOP package, which is available
    - Added ground pours to all layers
    - Used thermals on top and bottom to improve solderability
2022-04-12 Added 3D printable shell for creating ganged MMCX connection
    - Should make it easier for people to get the coax cable ordering
    correct at host
2022-08-22 Remove 2mm thick PCIe bracket
    - Too thick
    - 1.27 mm version is in spec, and should be used
2023-01-28 Create fmc-host - panel.brd
    Panel is a 2x2 with V-Cut and milling as separation method.
    The distance between individual boards is 5 mm.
2023-01-28 Added gerber files.
2023-03-29 first commit of metal PCIe bracket and LED PCB
    still need to source LEDs for LED PCB - common cathode/independent bottom-entry/revese-mounted LEDS turn out to be rare. PCIe bracket glue is pretty much good to go - LED hole positions are subject t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
2023-03-29 passes osh cut design check
    made a cut at the side 90 deg bend so the bend is like only half as long now. This is so that we don't get insufficient flange support warning
2023-03-30 LED PCB perpendicular to bracket
2023-03-30 added clearance for lens
2023-03-30 engraving finished. part w/ questionable flange to be tested in Oschut
2023-03-30 added logo for engraving if we want
2023-03-30 cleaned up pcie-metal-bracket folder
2023-03-31 production files added (i.e. gerber and dxf)
2023-04-03 gerbers and kicad ready for review
    gerber, bom, pnp files are in production folder for pcb fabrication and assembly. not sure if v-cut will be recognized by jlc. also, the individual pcbs are larger now with LEDs centered
2023-04-04 Update LED panel design after review
    - Reduce size to fit in current allowed volume
    - Move connector for improved strain relief
    - Match RGB pinout on fmc host
2023-04-28 fixed hole spacing, cleaned engraving
2023-04-28 hole diameters
2023-05-05 Fixed PCIe Bracket
    - hole spacing fixed
    - exploratory engravings removed
    - logo moved
    - mmcx hole diameter reduced to avoid thin features
2023-05-05 Fixed Schematic
    - LEDs remapped
    - Mounting pins grounded for mechanical integrity
    - Changed LED symbol (symbol is the same as KiCad generic symbol but
    with renumbered pins)
    - fiber optic included in schematic
2023-07-13 fixed pcb led-connector mapping
    be warned that schematic does not match pcb in an effort to get this to filipe for order asap
2026-03-31 Start KiCAD migration and address rev. F issues
    - Fix clashing reference selection on AD7616
    - Move from AD7617 to AD7616
    - Add TVS diodes to LVDS lines to the breakout board.
2026-05-08 Added OEPS PN
2026-05-28 Updated to latest OEPS PN and upgraded to KiCad 10
2026-06-30 Fix AD761x nRESET input
    - Replace 0.1uF filter capacitor with 100pF
    - Replace series 10k resistor with 0 ohm jumper
    - Add 10k pulldown so that chip power-on defaults to the reset state

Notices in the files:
fmc-host/fmc-host.sch:
LICENSE: SEE LICENSE FILE
